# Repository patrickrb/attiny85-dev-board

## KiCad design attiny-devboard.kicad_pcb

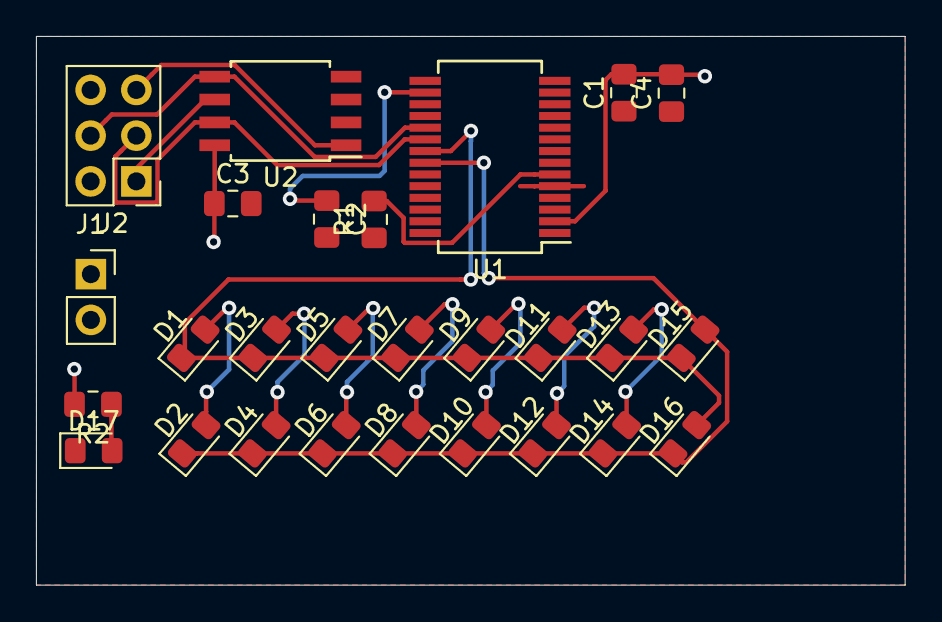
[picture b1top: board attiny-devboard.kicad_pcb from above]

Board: 2 copper layers, 48.3 x 30.5 mm, 27 parts (0 on the bottom side), 18 nets.

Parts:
C1: 1uF; C_0805_2012Metric_Pad1.15x1.40mm_HandSolder
C2: 0.1uF; C_0805_2012Metric_Pad1.15x1.40mm_HandSolder
C3: 100u; C_0805_2012Metric_Pad1.15x1.40mm_HandSolder
C4: .1uF; C_0805_2012Metric_Pad1.15x1.40mm_HandSolder
D1, D2, D3, D4, D5, D6, D7, D8, D9, D10, D11, D12, D13, D14, D15, D16, D17: LED; D_0805_2012Metric_Pad1.15x1.40mm_HandSolder
J1: POWER; PinSocket_1x02_P2.54mm_Vertical
J2: ICSP; PinHeader_2x03_P2.54mm_Vertical
R1: 20k; R_0805_2012Metric_Pad1.15x1.40mm_HandSolder
R2: R; R_0805_2012Metric_Pad1.15x1.40mm_HandSolder
U1: IS31FL3731-SA; SSOP-28_5.3x10.2mm_P0.65mm
U2: ATtiny85-20SU; SOIJ-8_5.3x5.3mm_P1.27mm

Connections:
+3V3: C1.2, C3.1, C4.2, J1.1, J2.2, R2.2, U1.2, U2.8
/CA1: D1.1, D3.1, D5.1, D7.1, D9.1, D11.1, D13.1, D15.1, D16.2, U1.21
/CA2: D2.1, D4.1, D6.1, D8.1, D10.1, D12.1, D14.1, D15.2, D16.1, U1.22
GND: C1.1, C2.2, C3.2, C4.1, D17.1, J1.2, J2.6, R1.1, U1.5, U2.4
MISO: J2.1, U2.6
MOSI: J2.4, U1.19, U2.5
unnamed: C2.1, U1.16
unnamed: D1.2, D2.2
unnamed: D3.2, D4.2
unnamed: D5.2, D6.2
unnamed: D7.2, D8.2
unnamed: D9.2, D10.2
unnamed: D11.2, D12.2
unnamed: D13.2, D14.2
unnamed: D17.2, R2.1
unnamed: R1.2, U1.6
RST: J2.5, U2.1
SCK: J2.3, U1.20, U2.7

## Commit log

2020-07-21 first commit, added leds
